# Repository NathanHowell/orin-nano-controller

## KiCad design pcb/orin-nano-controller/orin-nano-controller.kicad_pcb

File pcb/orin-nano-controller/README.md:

# Orin Nano Controller PCB Notes

## Jetson J14 Strap Control (`J2`)

Four Jetson boot/control straps land on the 12-pin right-angle socket (`J2`). They are driven by two SN74LVC2G07 dual open-drain buffers: `IC1` handles the APO and RESET lanes, `IC2` handles RECOVERY and POWER. The STM32 drives the buffer inputs on nets `OAPO`, `ORST`, `OREC`, and `OPWR`; each input has an on-board 100 kΩ pull-down (`RA0–RA3`) so the straps idle de-asserted while the MCU boots. The bench harness fans out to the Jetson front-panel header (`J14`, 2x7) using the cross-reference below.

| Jetson J14 pin | Jetson label | Controller J2 pin | Driver channel | MCU pin (net) | Active level | Harness notes |
| --- | --- | --- | --- | --- | --- | --- |
| 5 | `APO` (force shutdown) | 5 | `IC1` 1Y | PA5 (`OAPO`) | Assert by pulling low (MCU drives input high) | Ground return on J14-7 / J2-7 (GND) |
| 8 | `RESET*` | 8 | `IC1` 2Y | PA4 (`ORST`) | Assert low | Ground return on J14-9 / J2-9 (GND) |
| 10 | `REC*` (force recovery) | 10 | `IC2` 1Y | PA3 (`OREC`) | Assert low | Ground return on J14-11 / J2-11 (GND) |
| 12 | `PWR*` (power button) | 12 | `IC2` 2Y | PA2 (`OPWR`) | Assert low (200 ms pulse) | Shares ground return on J14-11 / J2-11 (GND) |

- Open-drain outputs only sink current; the Jetson carrier (or cable) must provide the pull-ups.
- Supply pin 5 of both buffers ties to the local `+3V3` rail.

## USB-C Front-End (`J3`)

- Receptacle: GCT USB4085-series (`J3`), wired as a USB 2.0 UFP. Shield (`S1`) bleeds to GND through `R1` (1 MΩ) while staying isolated from signal ground.
- CC pins: Both CC1 (`A5`) and CC2 (`B5`) populate 5.1 kΩ pull-downs (`RCC1`, `RCC0`) to advertise Rd as an upstream-facing device.
- Data path: D+ (A6/B6) and D− (A7/B7) run straight through the flow-through TVS array `D1` (Nexperia IP4220CZ6) before continuing on nets `/Controller/USB_DP` and `/Controller/USB_DM` into the STM32 pins PA12 and PA11. There are no discrete series resistors; route lengths rely on the ESD IC sitting directly behind the connector.
- VBUS: Pins A4/A9/B4/B9 feed `/Frontend/VBUS_RAW`, then through net tie `NT1` onto the `+5V` rail that powers the LDO. Place `D1` as close to the receptacle as possible to keep the stubs under ~1 mm, preserving the intended flow-through layout.

## Power Tree

- Source: USB VBUS (after `NT1`) becomes the `+5V` net. That net feeds the TLV75533 LDO (`U3`) input (pin 1) and its enable (pin 3), so the regulator is enabled whenever VBUS is present.
- Regulation: `U3` outputs the local 3.3 V rail on pin 5 (labelled `+3V3`, functionally the board’s `VDD_3V3`). Output decoupling is a 4.7 µF bulk cap (`C5`) plus local 100 nF/1 µF/100 nF caps (`C6`, `C7`, `C8`). Input decoupling uses 1 µF capacitors (`C2`, `C4`) on `+5V`.
- Load guidance: TLV75533P supports up to 500 mA continuous, but keep total draw (MCU, strap drivers, USB peripherals, downstream headers) comfortably below that to maintain headroom on USB-powered systems. The controller itself only needs on the order of a few tens of milliamps; reserve the remainder for anything you hang off J14.

## PC\_LED Sense Path

- The satellite harness brings the host “PC\_LED±” differential pair onto J14 pins 1–2 (`J2` pins 1–2). These drive the LED input of optocoupler `U1` (TLP185).
- The optocoupler transistor (pins 4/6) pulls STM32 pin PB2 low when lit. PB2 has a 10 kΩ pull-up to `+3V3` (`R3`), so:
  - LED off ⇒ PB2 ≈ 3.3 V (logic-high level for ADC/GPIO).
  - LED on with ≥1 mA LED current ⇒ PB2 pulled near ground (~0.2 V), sinking ≈0.33 mA through `R3`.
- There is no additional RC filtering; add digital filtering in firmware if the host LED toggles rapidly.

## SWD Header (`J1`, Arm 10-pin)

| Pin | Signal | Notes |
| --- | --- | --- |
| 1 | `+3V3` (VTref) | Target supply reference |
| 2 | `SWDIO` | To STM32 PA13 |
| 3 | GND | |
| 4 | `SWCLK` | To STM32 PA14 |
| 5 | GND | |
| 6 | `SWO` | To STM32 PB3 |
| 7 | KEY | No pin |
| 8 | NC/TDI | Not connected |
| 9 | GNDDetect | Hard-tied to GND |
| 10 | `~RESET` | To MCU `NRST` |

Take VTref from the on-board 3.3 V rail so external debuggers track the correct I/O voltage.

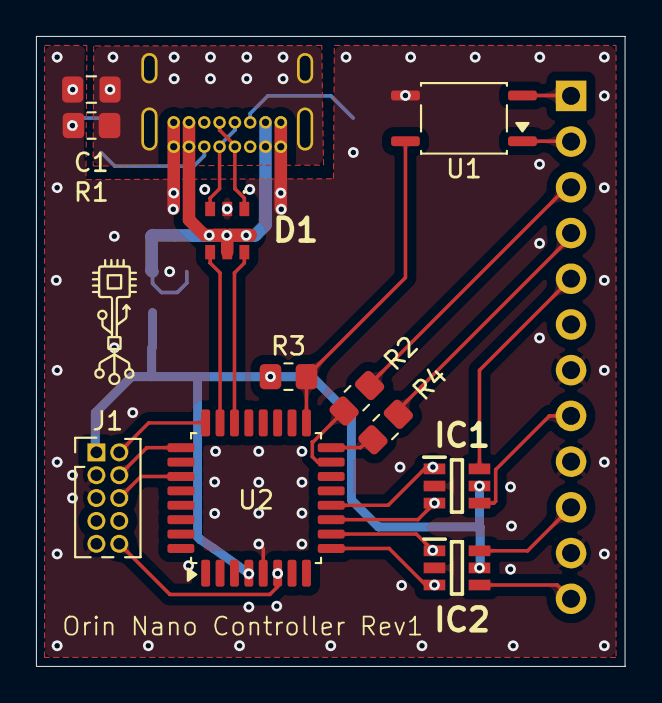
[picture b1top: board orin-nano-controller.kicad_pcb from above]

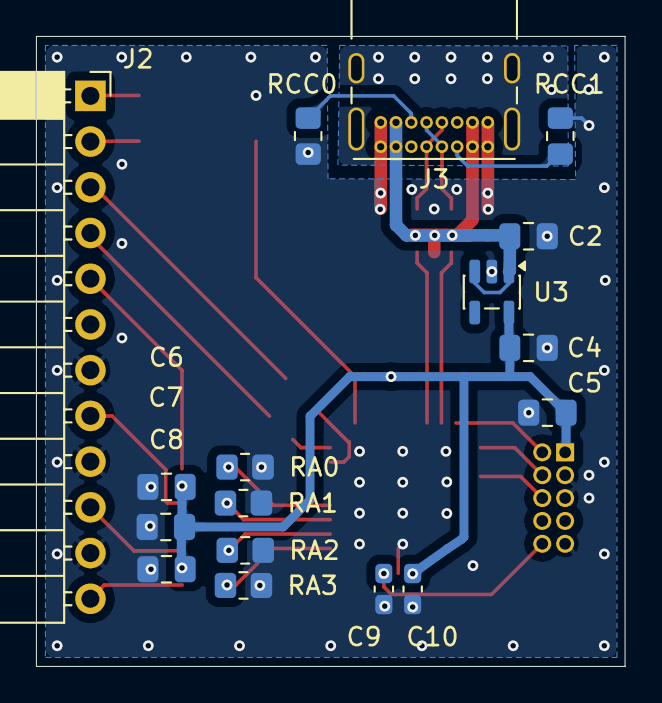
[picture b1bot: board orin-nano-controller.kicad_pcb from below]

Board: 4 copper layers, 32.7 x 35.0 mm, 29 parts (18 on the bottom side), 30 nets.

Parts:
C1: 2.2 nF; C_0805_2012Metric_Pad1.18x1.45mm_HandSolder
C2, C4, C7: 1 uF; C_0805_2012Metric_Pad1.18x1.45mm_HandSolder
C5: 4.7 uF; C_0805_2012Metric_Pad1.18x1.45mm_HandSolder
C6, C8: 0.1 uF; C_0805_2012Metric_Pad1.18x1.45mm_HandSolder
C9, C10: 0.1 uF; C_0603_1608Metric_Pad1.08x0.95mm_HandSolder
D1: IP4220CZ6
IC1, IC2: SN74LVC2G07DBVR; SOT95P280X145-6N
J1: Conn_ARM_JTAG_SWD_10; PinHeader_2x05_P1.27mm_Vertical
J2: Conn_01x12_Socket; PinSocket_1x12_P2.54mm_Horizontal
J3: USB_C_Receptacle_USB2.0_14P; USB_C_Receptacle_GCT_USB4085
NT1: NetTie_2; NetTie-2_SMD_Pad0.5mm
R1: 1 MΩ; R_0805_2012Metric_Pad1.20x1.40mm_HandSolder
R2, R4: 33 Ω; R_0805_2012Metric_Pad1.20x1.40mm_HandSolder
R3: 10 kΩ; R_0805_2012Metric_Pad1.20x1.40mm_HandSolder
RA0, RA1, RA2, RA3: 100 kΩ; R_0805_2012Metric_Pad1.20x1.40mm_HandSolder
RCC0, RCC1: 5.1 kΩ; R_0805_2012Metric_Pad1.20x1.40mm_HandSolder
U1: TLP185xSE; SOIC-4_4.55x3.7mm_P2.54mm
U2: STM32G0B1KETx; LQFP-32_7x7mm_P0.8mm
U3: TLV75533PDBV; SOT-23-5

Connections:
+3V3: C4.1, C5.1, C6.1, C7.1, C8.1, C10.1, IC1.5 (VCC), IC2.5 (VCC), J1.1 (VTref), R3.1, U2.4 (VDD), U3.5 (OUT)
+5V: C2.1, NT1.2, U3.1 (IN), U3.3 (EN)
/Controller/APO_STRAP: IC1.6 (1Y), J2.5
/Controller/PWR_STRAP: IC2.4 (2Y), J2.12
/Controller/REC_STRAP: IC2.6 (1Y), J2.10
/Controller/RST_STRAP: IC1.4 (2Y), J2.8
/Controller/USB_DM: D1.6 (I/O_4), U2.22 (PA9/PA11)
/Controller/USB_DP: D1.4 (I/O_3), U2.23 (PA10/PA12)
/Frontend/USB_DM_CONN: D1.1 (I/O_1), J3.A7 (D-), J3.B7 (D-)
/Frontend/USB_DP_CONN: D1.3 (I/O_2), J3.A6 (D+), J3.B6 (D+)
/Frontend/VBUS_RAW: D1.5 (VP), J3.A4 (VBUS), J3.A9 (VBUS), J3.B4 (VBUS), J3.B9 (VBUS), NT1.1
GND: C1.2, C2.2, C4.2, C5.2, C6.2, C7.2, C8.2, C9.2, C10.2, D1.2 (GND), IC1.2 (GND), IC2.2 (GND), J1.3 (GND), J1.5 (GND), J1.9 (GNDDetect), J2.7, J2.9, J2.11, J3.A1 (GND), J3.A12 (GND), J3.B1 (GND), J3.B12 (GND), R1.2, RA0.2, RA1.2, RA2.2, RA3.2, RCC0.2, RCC1.2, U1.4, U2.5 (VSS), U3.2 (GND)
GNDREF: C1.1, J3.S1 (SHIELD), R1.1
NRST: C9.1, J1.10 (~RESET), U2.6 (PF2)
unnamed: J3.A5 (CC1), RCC1.1
unnamed: J3.B5 (CC2), RCC0.1
unnamed: R2.2, U2.15 (PB0)
unnamed: R4.2, U2.16 (PB1)
OAPO: IC1.1 (1A), RA0.1, U2.12 (PA5)
OPWR: IC2.3 (2A), RA3.1, U2.9 (PA2)
OREC: IC2.1 (1A), RA2.1, U2.10 (PA3)
ORST: IC1.3 (2A), RA1.1, U2.11 (PA4)
PB2: R3.2, U1.6, U2.17 (PB2)
PC_LED+: J2.2, U1.1
PC_LED-: J2.1, U1.3
SWCLK: J1.4 (SWCLK/TCK), U2.25 (PA14)
SWDIO: J1.2 (SWDIO/TMS), U2.24 (PA13)
SWO: J1.6 (SWO/TDO), U2.27 (PB3)
UART2_RXD: J2.3, R2.1
UART2_TXD: J2.4, R4.1

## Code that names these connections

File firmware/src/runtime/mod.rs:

use cortex_m::interrupt;
use cortex_m::register::primask;
use critical_section::{self, RawRestoreState};
use defmt_rtt as _;
use embassy_executor::Spawner;
use embassy_stm32 as hal;
use embassy_stm32::gpio::{Level, OutputOpenDrain, Speed};
use embassy_sync::channel::Channel;

use crate::bridge::{BridgeActivityBus, BridgeQueue};
use crate::hw::power;
use crate::straps;
use crate::straps::orchestrator::{HardwareStrapDriver, StrapOrchestrator};
use crate::telemetry::TelemetryRecorder;
use crate::usb;
use controller_core::orchestrator::{VrefintPowerMonitor, register_default_templates};
use embassy_stm32::adc::Adc;
use static_cell::StaticCell;

mod bridge_task;
mod repl_task;
mod strap_task;
mod usb_task;

critical_section::set_impl!(InterruptCriticalSection);

struct InterruptCriticalSection;

unsafe impl critical_section::Impl for InterruptCriticalSection {
    unsafe fn acquire() -> RawRestoreState {
        let primask = primask::read();
        interrupt::disable();
        primask.is_active()
    }

    unsafe fn release(restore_state: RawRestoreState) {
        if restore_state {
            unsafe {
                interrupt::enable();
            }
        }
    }
}

pub(super) static COMMAND_QUEUE: straps::CommandQueue = Channel::new();
pub(super) static BRIDGE_QUEUE: BridgeQueue = BridgeQueue::new();
pub(super) static BRIDGE_ACTIVITY: BridgeActivityBus = BridgeActivityBus::new();
pub(super) static USB_STORAGE: StaticCell<usb::UsbDeviceStorage> = StaticCell::new();

#[embassy_executor::main]
pub async fn main(spawner: Spawner) {
    let config = hal::Config::default();
    let hal::Peripherals {
        PA2,
        PA3,
        PA4,
        PA5,
        PB0,
        PB1,
        USB,
        PA11,
        PA12,
        ADC1,
        USART5,
        ..
    } = hal::init(config);

    let strap_driver = HardwareStrapDriver::new(
        OutputOpenDrain::new(PA4, Level::High, Speed::Low),
        OutputOpenDrain::new(PA3, Level::High, Speed::Low),
        OutputOpenDrain::new(PA2, Level::High, Speed::Low),
        OutputOpenDrain::new(PA5, Level::High, Speed::Low),
    );

    let adc = Adc::new(ADC1);
    let sample_provider = power::VrefintAdc::new(adc);
    let calibration = power::read_vrefint_calibration();
    let power_monitor = VrefintPowerMonitor::new(calibration, sample_provider);

    let command_receiver = COMMAND_QUEUE.receiver();
    let mut orchestrator =
        StrapOrchestrator::with_components(command_receiver, power_monitor, strap_driver);
    {
        let registry = orchestrator.templates_mut();
        register_default_templates(registry).expect("strap template registration");
    }

    let telemetry = TelemetryRecorder::new();

    spawner
        .spawn(strap_task::run(orchestrator, telemetry))
        .expect("failed to spawn strap orchestrator task");

    spawner
        .spawn(usb_task::run(USB, PA12, PA11))
        .expect("failed to spawn USB task");

    spawner
        .spawn(repl_task::run())
        .expect("failed to spawn REPL task");
    spawner
        .spawn(bridge_task::run(
            &BRIDGE_QUEUE,
            &BRIDGE_ACTIVITY,
            USART5,
            PB0,
            PB1,
        ))
        .expect("failed to spawn bridge task");

    core::future::pending::<()>().await;
}

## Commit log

2025-10-16 Root commit
2025-10-16 Initial add
2025-10-16 stubbing
2025-10-17 Initial plan
2025-10-17 Add comprehensive schematic review and component checklist
2025-10-17 Add schematic hierarchy, review summary, and navigation guide
2025-10-17 Add printable review report
2025-10-21 remove some vias
2025-10-22 rev 1
2025-10-23 part updates
2025-10-23 replace ldo
2025-10-23 update gitignore
2025-10-23 update components
2025-10-23 refill zones
2025-10-23 docs: adopt constitution v1.0.0 with hardware governance
2025-10-23 Document hardware interfaces
2025-10-24 specs: refresh 001-build-orin-controller artifacts
2025-10-24 docs: sync AGENTS with current plan
2025-10-24 add justfile
2025-10-24 Align Orin controller spec, plan, and tasks
2025-10-24 T002: add bench instrumentation checklist
2025-10-24 T003: default to thumbv6m target
2025-10-24 T004 pin workspace toolchain
2025-10-24 T005: add strap data model scaffolding
2025-10-24 Add host dummy test harness
2025-10-24 feat(straps): add orchestrator skeleton scaffolding
2025-10-24 Implement telemetry ring buffer scaffolding
2025-10-24 Add queued command telemetry and orchestrator queue
2025-10-24 T008: scaffold USB UART bridge channels
2025-10-24 Fix clippy warning for bridge activity monitor
2025-10-24 Implement REPL scaffolding for CDC0 (T009)
2025-10-25 Implement dual-CDC USB scaffold
2025-10-25 Wire initial Embassy runtime scaffolding
2025-10-25 Implement brown-out retry handling
2025-10-25 Fix clippy warnings
2025-10-25 Handle USB control link disconnect safe-state
2025-10-25 Add NormalReboot strap sequence template
2025-10-25 Implement queue-driven NormalReboot execution
2025-10-25 feat(repl): add reboot command with optional delay
2025-10-25 Add normal reboot sequence completion telemetry
2025-10-25 docs: amend constitution to v1.1.0 for core/emulator split
2025-10-25 docs: align 001 spec/plan with controller-core split
2025-10-25 docs: refresh 001 tasks for controller-core split
2025-10-25 docs: refresh constitution check and mark T001
2025-10-25 Document bench instrumentation readiness
2025-10-25 Document rust toolchain pin alignment
2025-10-25 Record default thumbv6m target configuration
2025-10-25 Scaffold controller-core crate
2025-10-25 Align workspace for shared crates
2025-10-25 add reminders about migration
2025-10-25 Update telemetry logging spec to defmt stream
2025-10-25 Update constitution
2025-10-25 Add orchestrator interfaces for controller core
2025-10-25 Implement shared strap sequence data structures
2025-10-25 Implement controller-core REPL grammar
2025-10-25 Add shared telemetry definitions to controller-core
2025-10-25 Add firmware adapters for controller-core
2025-10-25 Scaffold emulator host REPL entrypoint
2025-10-25 Add just target for controller-core smoke builds
2025-10-25 feat(controller-core): add normal reboot sequence
2025-10-25 Add scheduler helpers for NormalReboot cooldown
2025-10-25 Implement shared reboot command dispatcher
2025-10-26 Add NormalReboot timing unit tests
2025-10-26 Bind strap driver to hardware for normal reboot
2025-10-26 Implement emulator reboot session logging
2025-10-26 Add recovery sequence templates
2025-10-26 Add bridge hold helpers for recovery sequences
2025-10-26 Publish bridge telemetry for recovery
2025-10-26 Implement recovery REPL commands
2025-10-27 feat(emulator): add recovery transcript profile
2025-10-27 Add recovery sequence host tests
2025-10-27 Add firmware wiring follow-up tasks
2025-10-27 Refactor firmware REPL helpers
2025-10-27 Add follow-up firmware REPL tasks
2025-10-27 firmware: drop legacy strap scaffolding
2025-10-27 bump deps
2025-10-27 Mark T053 complete for Embassy USB alignment
2025-10-27 Wire firmware REPL session plumbing
2025-10-27 Fix host clippy for REPL queues
2025-10-27 T051: rebuild firmware REPL task around shared executor
2025-10-27 T052: implement USB dual CDC task
2025-10-27 feat(firmware): wire jetson uart bridge
2025-10-27 Add fault recovery sequence template
2025-10-27 Implement fault recovery command retries and telemetry
2025-10-27 Add tab completion tasks
2025-10-27 Add grammar-aware REPL completion engine
2025-10-27 Implement firmware REPL tab completion
2025-10-27 Fix clippy warnings in REPL completion
2025-10-27 Add emulator tab completion parity
2025-10-27 Handle fault recovery retries in firmware orchestrator
2025-10-28 add new just targets
2025-10-28 Load full strap templates on firmware startup
2025-10-28 Add fault recovery parity transcript
2025-10-28 Refactor firmware USB interfaces
2025-10-28 cargo fmt
2025-10-28 Use embassy memory script and enable defmt logger
2025-10-28 Add fault recovery retry tests
2025-10-28 Add Phase 6 backlog tasks for controller refactors
2025-10-28 Refactor orchestrator runtime into controller core for shared use
2025-10-28 T059: use shared TemplateRegistry
2025-10-28 Move SequenceRun state into controller-core
2025-10-28 T061: move bridge monitor and telemetry recorder into core
2025-10-28 T062: split firmware tasks into runtime modules
2025-10-28 T040: resolve clippy warnings
2025-10-28 T063: centralize strap template registration
2025-10-28 T064: share power monitor abstraction
2025-10-28 Plan: queue VREFINT brown-out tasks
2025-10-28 T065: document VREFINT brown-out design
2025-10-28 T066: add VREFINT power monitor
2025-10-28 Fix firmware build entrypoint
2025-10-28 T067: add STM32G0 VREFINT sampling helper
2025-10-28 T068: wire firmware to Vrefint power monitor
2025-10-28 Completion: append space via replacement flag
2025-10-28 Move PCB project to pcb root
2025-10-28 Switch REPL lexer to regal
2025-10-28 Refactor REPL grammar into applicative DSL
2025-10-29 Implement atomic status snapshot and enable firmware status command
2025-10-29 Detect debugger link in firmware status snapshot
2025-10-29 Centralize status formatting and add debugger line
2025-10-29 Centralize status tracking helpers
2025-10-29 Use Duration constants in strap sequences
2025-10-29 add a panic handler
2025-10-29 expose the stm32 serial number through usb
2025-10-29 Use StaticCell for firmware statics
2025-10-29 simplify lifetimes
2025-10-29 Fix pedantic clippy violations
2025-10-29 Adjust core for dependency upgrades
2025-10-29 Use git Regal dependencies
2025-10-30 fix cargo lint warning
2025-10-30 Fix emulator completion prefix application
2025-10-30 Name USB descriptor constants
2025-10-30 Rustfmt cleanup after toolchain update
2025-10-30 Bump toolchain to Rust 1.91.0
